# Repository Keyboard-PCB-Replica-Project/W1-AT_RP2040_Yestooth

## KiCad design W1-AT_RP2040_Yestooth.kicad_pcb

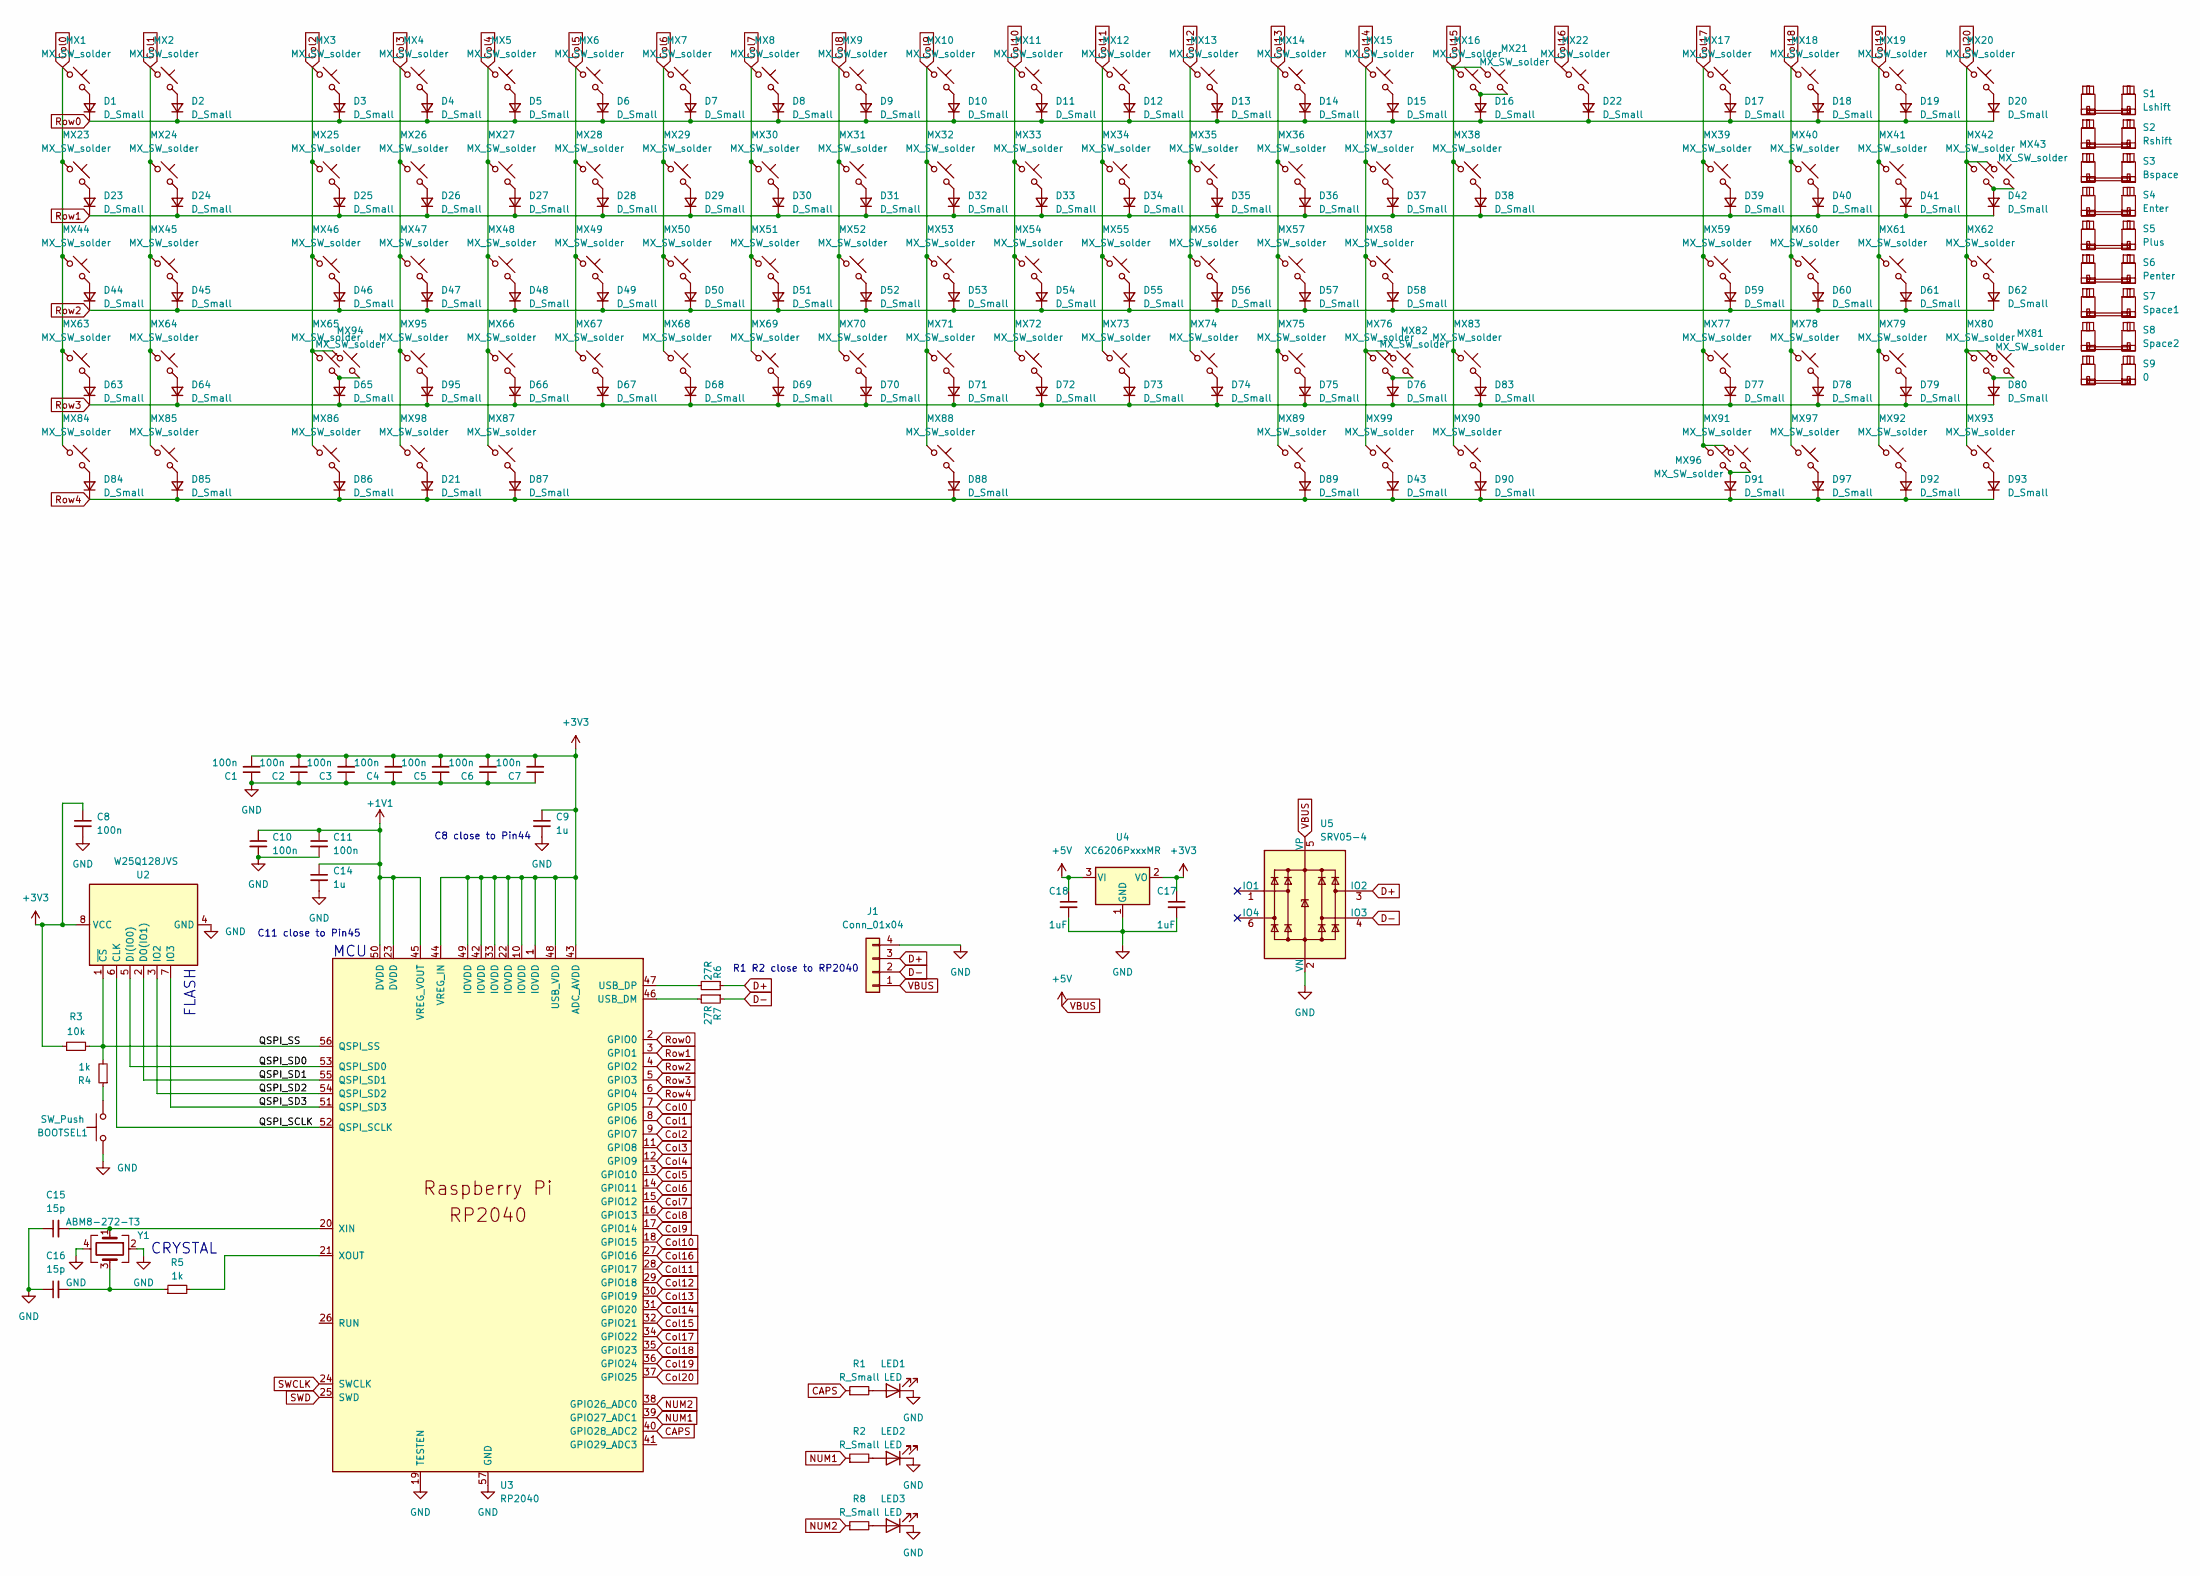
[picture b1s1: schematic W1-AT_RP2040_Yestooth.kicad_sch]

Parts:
BOOTSEL1: SW_Push; SW_Push_1P1T_XKB_TS-1187A
C1, C2, C3, C4, C5, C6, C7, C8, C10, C11: 100n; C_0402_1005Metric
C9, C14: 1u; C_0402_1005Metric
C15, C16: 15p; C_0402_1005Metric
C17, C18: 1uF; C_0402_1005Metric
D1, D2, D3, D4, D5, D6, D7, D8, D9, D10, D11, D12, D13, D14, D15, D16, D17, D18, D19, D20, D21, D22, D23, D24, D25, D26, D27, D28, D29, D30, D31, D32, D33, D34, D35, D36, D37, D38, D39, D40, D41, D42, D43, D44, D45, D46, D47, D48, D49, D50, D51, D52, D53, D54, D55, D56, D57, D58, D59, D60, D61, D62, D63, D64, D65, D66, D67, D68, D69, D70, D71, D72, D73, D74, D75, D76, D77, D78, D79, D80, D83, D84, D85, D86, D87, D88, D89, D90, D91, D92, D93, D95, D97: D_Small; Diode_SOD-123_noref
J1: Conn_01x04; JST_SH_SM04B-SRSS-TB_1x04-1MP_P1.00mm_Horizontal
LED1, LED2, LED3: LED; KT-0805W
MX1, MX2, MX3, MX4, MX5, MX6, MX7, MX8, MX9, MX10, MX11, MX12, MX13, MX14, MX15, MX16, MX17, MX18, MX19, MX20, MX21, MX22, MX23, MX24, MX25, MX26, MX27, MX28, MX29, MX30, MX31, MX32, MX33, MX34, MX35, MX36, MX37, MX38, MX39, MX40, MX41, MX42, MX43, MX44, MX45, MX46, MX47, MX48, MX49, MX50, MX51, MX52, MX53, MX54, MX55, MX56, MX57, MX58, MX59, MX60, MX61, MX62, MX63, MX64, MX65, MX66, MX67, MX68, MX69, MX70, MX71, MX72, MX73, MX74, MX75, MX76, MX77, MX78, MX79, MX80, MX81, MX82, MX83, MX84, MX85, MX86, MX87, MX88, MX89, MX90, MX91, MX92, MX93, MX94, MX95, MX96, MX97, MX98, MX99: MX_SW_solder; MX_PCB_1.00u_NoSilkscreen_narrow
R1, R2, R8: R_Small; R_0805_2012Metric
R3: 10k; R_0402_1005Metric
R4, R5: 1k; R_0402_1005Metric
R6, R7: 27R; C_0805_2012Metric
S1: Lshift; Stabilizer_MX_2.00u
S2: Rshift; Stabilizer_MX_2.00u
S3: Bspace; Stabilizer_MX_2.00u
S4: Enter; Stabilizer_MX_2.00u
S5: Plus; Stabilizer_MX_2.00u
S6: Penter; Stabilizer_MX_2.00u
S7: Space1; Stabilizer_MX_7.00u
S8: Space2; Stabilizer_MX_8.00u
S9: 0; Stabilizer_MX_2.00u
U2: W25Q128JVS; SOIC-8_5.23x5.23mm_P1.27mm
U3: RP2040; RP2040-QFN-56
U4: XC6206PxxxMR; SOT-23
U5: SRV05-4; SOT-23-6
Y1: ABM8-272-T3; Oscillator_SMD_EuroQuartz_XO32-4Pin_3.2x2.5mm

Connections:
+1V1: C10.1, C11.1, C14.1, U3.23 (DVDD), U3.45 (VREG_VOUT), U3.50 (DVDD)
+3V3: C1.2, C2.2, C3.2, C4.2, C5.2, C6.2, C7.2, C8.1, C9.1, C17.1, R3.1, U2.8 (VCC), U3.1 (IOVDD), U3.10 (IOVDD), U3.22 (IOVDD), U3.33 (IOVDD), U3.42 (IOVDD), U3.43 (ADC_AVDD), U3.44 (VREG_IN), U3.48 (USB_VDD), U3.49 (IOVDD), U4.2 (VO)
/QSPI_SCLK: U2.6 (CLK), U3.52 (QSPI_SCLK)
/QSPI_SD0: U2.5 (DI(IO0)), U3.53 (QSPI_SD0)
/QSPI_SD1: U2.2 (DO(IO1)), U3.55 (QSPI_SD1)
/QSPI_SD2: U2.3 (IO2), U3.54 (QSPI_SD2)
/QSPI_SD3: U2.7 (IO3), U3.51 (QSPI_SD3)
/QSPI_SS: R3.2, R4.2, U2.1 (~CS), U3.56 (QSPI_SS)
CAPS: R1.1, U3.40 (GPIO28_ADC2)
Col0: MX1.1, MX23.1, MX44.1, MX63.1, MX84.1, U3.7 (GPIO5)
Col1: MX2.1, MX24.1, MX45.1, MX64.1, MX85.1, U3.8 (GPIO6)
Col2: MX3.1, MX25.1, MX46.1, MX65.1, MX86.1, MX94.1, U3.9 (GPIO7)
Col3: MX4.1, MX26.1, MX47.1, MX95.1, MX98.1, U3.11 (GPIO8)
Col4: MX5.1, MX27.1, MX48.1, MX66.1, MX87.1, U3.12 (GPIO9)
Col5: MX6.1, MX28.1, MX49.1, MX67.1, U3.13 (GPIO10)
Col6: MX7.1, MX29.1, MX50.1, MX68.1, U3.14 (GPIO11)
Col7: MX8.1, MX30.1, MX51.1, MX69.1, U3.15 (GPIO12)
Col8: MX9.1, MX31.1, MX52.1, MX70.1, U3.16 (GPIO13)
Col9: MX10.1, MX32.1, MX53.1, MX71.1, MX88.1, U3.17 (GPIO14)
Col10: MX11.1, MX33.1, MX54.1, MX72.1, U3.18 (GPIO15)
Col11: MX12.1, MX34.1, MX55.1, MX73.1, U3.28 (GPIO17)
Col12: MX13.1, MX35.1, MX56.1, MX74.1, U3.29 (GPIO18)
Col13: MX14.1, MX36.1, MX57.1, MX75.1, MX89.1, U3.30 (GPIO19)
Col14: MX15.1, MX37.1, MX58.1, MX76.1, MX82.1, MX99.1, U3.31 (GPIO20)
Col15: MX16.1, MX21.1, MX38.1, MX83.1, MX90.1, U3.32 (GPIO21)
Col16: MX22.1, U3.27 (GPIO16)
Col17: MX17.1, MX39.1, MX59.1, MX77.1, MX91.1, MX96.1, U3.34 (GPIO22)
Col18: MX18.1, MX40.1, MX60.1, MX78.1, MX97.1, U3.35 (GPIO23)
Col19: MX19.1, MX41.1, MX61.1, MX79.1, MX92.1, U3.36 (GPIO24)
Col20: MX20.1, MX42.1, MX43.1, MX62.1, MX80.1, MX81.1, MX93.1, U3.37 (GPIO25)
D+: J1.3, R6.1, U5.3 (IO2)
D-: J1.2, R7.1, U5.4 (IO3)
GND: BOOTSEL1.1, C1.1, C2.1, C3.1, C4.1, C5.1, C6.1, C7.1, C8.2, C9.2, C10.2, C11.2, C14.2, C15.1, C16.1, C17.2, C18.2, J1.4, LED1.1 (K), LED2.1 (K), LED3.1 (K), U2.4 (GND), U3.19 (TESTEN), U3.57 (GND), U4.1 (GND), U5.2 (VN), Y1.2, Y1.4
NUM1: R2.1, U3.39 (GPIO27_ADC1)
NUM2: R8.1, U3.38 (GPIO26_ADC0)
unnamed: BOOTSEL1.2, R4.1
unnamed: C16.2, R5.1, Y1.3
unnamed: D1.2 (A), MX1.2
unnamed: D2.2 (A), MX2.2
unnamed: D3.2 (A), MX3.2
unnamed: D4.2 (A), MX4.2
unnamed: D5.2 (A), MX5.2
unnamed: D6.2 (A), MX6.2
unnamed: D7.2 (A), MX7.2
unnamed: D8.2 (A), MX8.2
unnamed: D9.2 (A), MX9.2
unnamed: D10.2 (A), MX10.2
unnamed: D11.2 (A), MX11.2
unnamed: D12.2 (A), MX12.2
unnamed: D13.2 (A), MX13.2
unnamed: D14.2 (A), MX14.2
unnamed: D15.2 (A), MX15.2
unnamed: D16.2 (A), MX16.2, MX21.2
unnamed: D17.2 (A), MX17.2
unnamed: D18.2 (A), MX18.2
unnamed: D19.2 (A), MX19.2
unnamed: D20.2 (A), MX20.2
unnamed: D21.2 (A), MX98.2
unnamed: D22.2 (A), MX22.2
unnamed: D23.2 (A), MX23.2
unnamed: D24.2 (A), MX24.2
unnamed: D25.2 (A), MX25.2
unnamed: D26.2 (A), MX26.2
unnamed: D27.2 (A), MX27.2
unnamed: D28.2 (A), MX28.2
unnamed: D29.2 (A), MX29.2
unnamed: D30.2 (A), MX30.2
unnamed: D31.2 (A), MX31.2
unnamed: D32.2 (A), MX32.2
unnamed: D33.2 (A), MX33.2
unnamed: D34.2 (A), MX34.2
unnamed: D35.2 (A), MX35.2
unnamed: D36.2 (A), MX36.2
unnamed: D37.2 (A), MX37.2
unnamed: D38.2 (A), MX38.2
unnamed: D39.2 (A), MX39.2
unnamed: D40.2 (A), MX40.2
unnamed: D41.2 (A), MX41.2
unnamed: D42.2 (A), MX42.2, MX43.2
unnamed: D43.2 (A), MX99.2
unnamed: D44.2 (A), MX44.2
unnamed: D45.2 (A), MX45.2
unnamed: D46.2 (A), MX46.2
unnamed: D47.2 (A), MX47.2
unnamed: D48.2 (A), MX48.2
unnamed: D49.2 (A), MX49.2
unnamed: D50.2 (A), MX50.2
unnamed: D51.2 (A), MX51.2
unnamed: D52.2 (A), MX52.2
unnamed: D53.2 (A), MX53.2
unnamed: D54.2 (A), MX54.2
unnamed: D55.2 (A), MX55.2
unnamed: D56.2 (A), MX56.2
unnamed: D57.2 (A), MX57.2
unnamed: D58.2 (A), MX58.2
unnamed: D59.2 (A), MX59.2
unnamed: D60.2 (A), MX60.2
unnamed: D61.2 (A), MX61.2
unnamed: D62.2 (A), MX62.2
unnamed: D63.2 (A), MX63.2
unnamed: D64.2 (A), MX64.2
unnamed: D65.2 (A), MX65.2, MX94.2
unnamed: D66.2 (A), MX66.2
unnamed: D67.2 (A), MX67.2
unnamed: D68.2 (A), MX68.2
unnamed: D69.2 (A), MX69.2
unnamed: D70.2 (A), MX70.2
unnamed: D71.2 (A), MX71.2
unnamed: D72.2 (A), MX72.2
unnamed: D73.2 (A), MX73.2
unnamed: D74.2 (A), MX74.2
unnamed: D75.2 (A), MX75.2
unnamed: D76.2 (A), MX76.2, MX82.2
unnamed: D77.2 (A), MX77.2
unnamed: D78.2 (A), MX78.2
unnamed: D79.2 (A), MX79.2
unnamed: D80.2 (A), MX80.2, MX81.2
unnamed: D83.2 (A), MX83.2
unnamed: D84.2 (A), MX84.2
unnamed: D85.2 (A), MX85.2
unnamed: D86.2 (A), MX86.2
unnamed: D87.2 (A), MX87.2
unnamed: D88.2 (A), MX88.2
unnamed: D89.2 (A), MX89.2
unnamed: D90.2 (A), MX90.2
unnamed: D91.2 (A), MX91.2, MX96.2
unnamed: D92.2 (A), MX92.2
unnamed: D93.2 (A), MX93.2
unnamed: D95.2 (A), MX95.2
unnamed: D97.2 (A), MX97.2
unnamed: LED1.2 (A), R1.2
unnamed: LED2.2 (A), R2.2
unnamed: LED3.2 (A), R8.2
unnamed: R7.2, U3.46 (USB_DM)
unnamed: R6.2, U3.47 (USB_DP)
unnamed: C15.2, U3.20 (XIN), Y1.1
unnamed: R5.2, U3.21 (XOUT)
Row0: D1.1 (K), D2.1 (K), D3.1 (K), D4.1 (K), D5.1 (K), D6.1 (K), D7.1 (K), D8.1 (K), D9.1 (K), D10.1 (K), D11.1 (K), D12.1 (K), D13.1 (K), D14.1 (K), D15.1 (K), D16.1 (K), D17.1 (K), D18.1 (K), D19.1 (K), D20.1 (K), D22.1 (K), U3.2 (GPIO0)
Row1: D23.1 (K), D24.1 (K), D25.1 (K), D26.1 (K), D27.1 (K), D28.1 (K), D29.1 (K), D30.1 (K), D31.1 (K), D32.1 (K), D33.1 (K), D34.1 (K), D35.1 (K), D36.1 (K), D37.1 (K), D38.1 (K), D39.1 (K), D40.1 (K), D41.1 (K), D42.1 (K), U3.3 (GPIO1)
Row2: D44.1 (K), D45.1 (K), D46.1 (K), D47.1 (K), D48.1 (K), D49.1 (K), D50.1 (K), D51.1 (K), D52.1 (K), D53.1 (K), D54.1 (K), D55.1 (K), D56.1 (K), D57.1 (K), D58.1 (K), D59.1 (K), D60.1 (K), D61.1 (K), D62.1 (K), U3.4 (GPIO2)
Row3: D63.1 (K), D64.1 (K), D65.1 (K), D66.1 (K), D67.1 (K), D68.1 (K), D69.1 (K), D70.1 (K), D71.1 (K), D72.1 (K), D73.1 (K), D74.1 (K), D75.1 (K), D76.1 (K), D77.1 (K), D78.1 (K), D79.1 (K), D80.1 (K), D83.1 (K), D95.1 (K), U3.5 (GPIO3)
Row4: D21.1 (K), D43.1 (K), D84.1 (K), D85.1 (K), D86.1 (K), D87.1 (K), D88.1 (K), D89.1 (K), D90.1 (K), D91.1 (K), D92.1 (K), D93.1 (K), D97.1 (K), U3.6 (GPIO4)
SWCLK: U3.24 (SWCLK)
SWD: U3.25 (SWD)
VBUS: C18.1, J1.1, U4.3 (VI), U5.5 (VP)

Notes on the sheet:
C8 close to Pin44
MCU
C11 close to Pin45
R1 R2 close to RP2040
CRYSTAL
FLASH

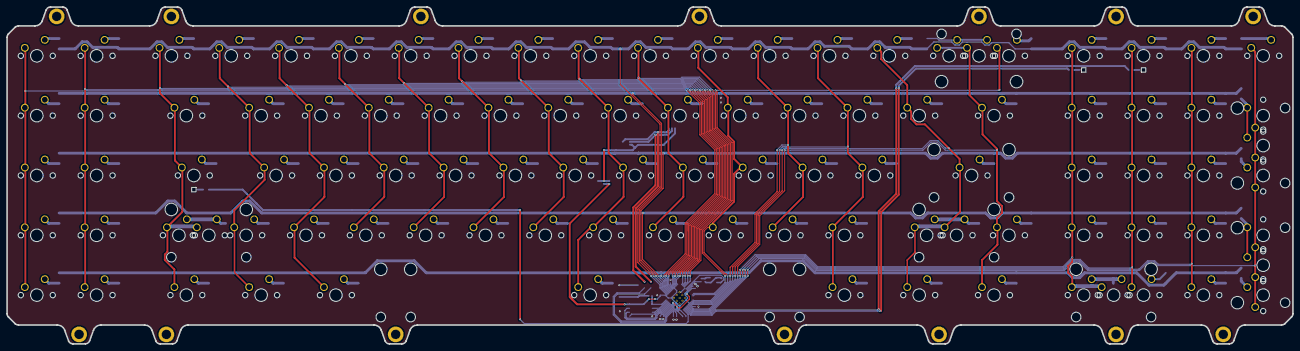
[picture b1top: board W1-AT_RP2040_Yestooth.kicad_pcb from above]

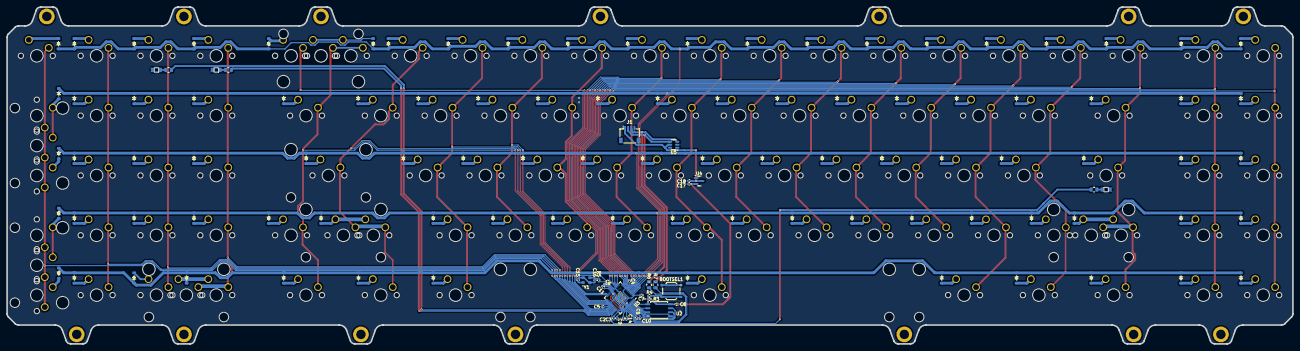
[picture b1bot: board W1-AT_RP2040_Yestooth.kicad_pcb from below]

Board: 2 copper layers, 409.5 x 107.3 mm, 249 parts (127 on the bottom side), 143 nets.

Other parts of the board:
H1, H2, H3, H4, H5, H6, H7, H8, H10, H10#2, H11, H12, H13, H14: MountingHole; tadpole_hole
